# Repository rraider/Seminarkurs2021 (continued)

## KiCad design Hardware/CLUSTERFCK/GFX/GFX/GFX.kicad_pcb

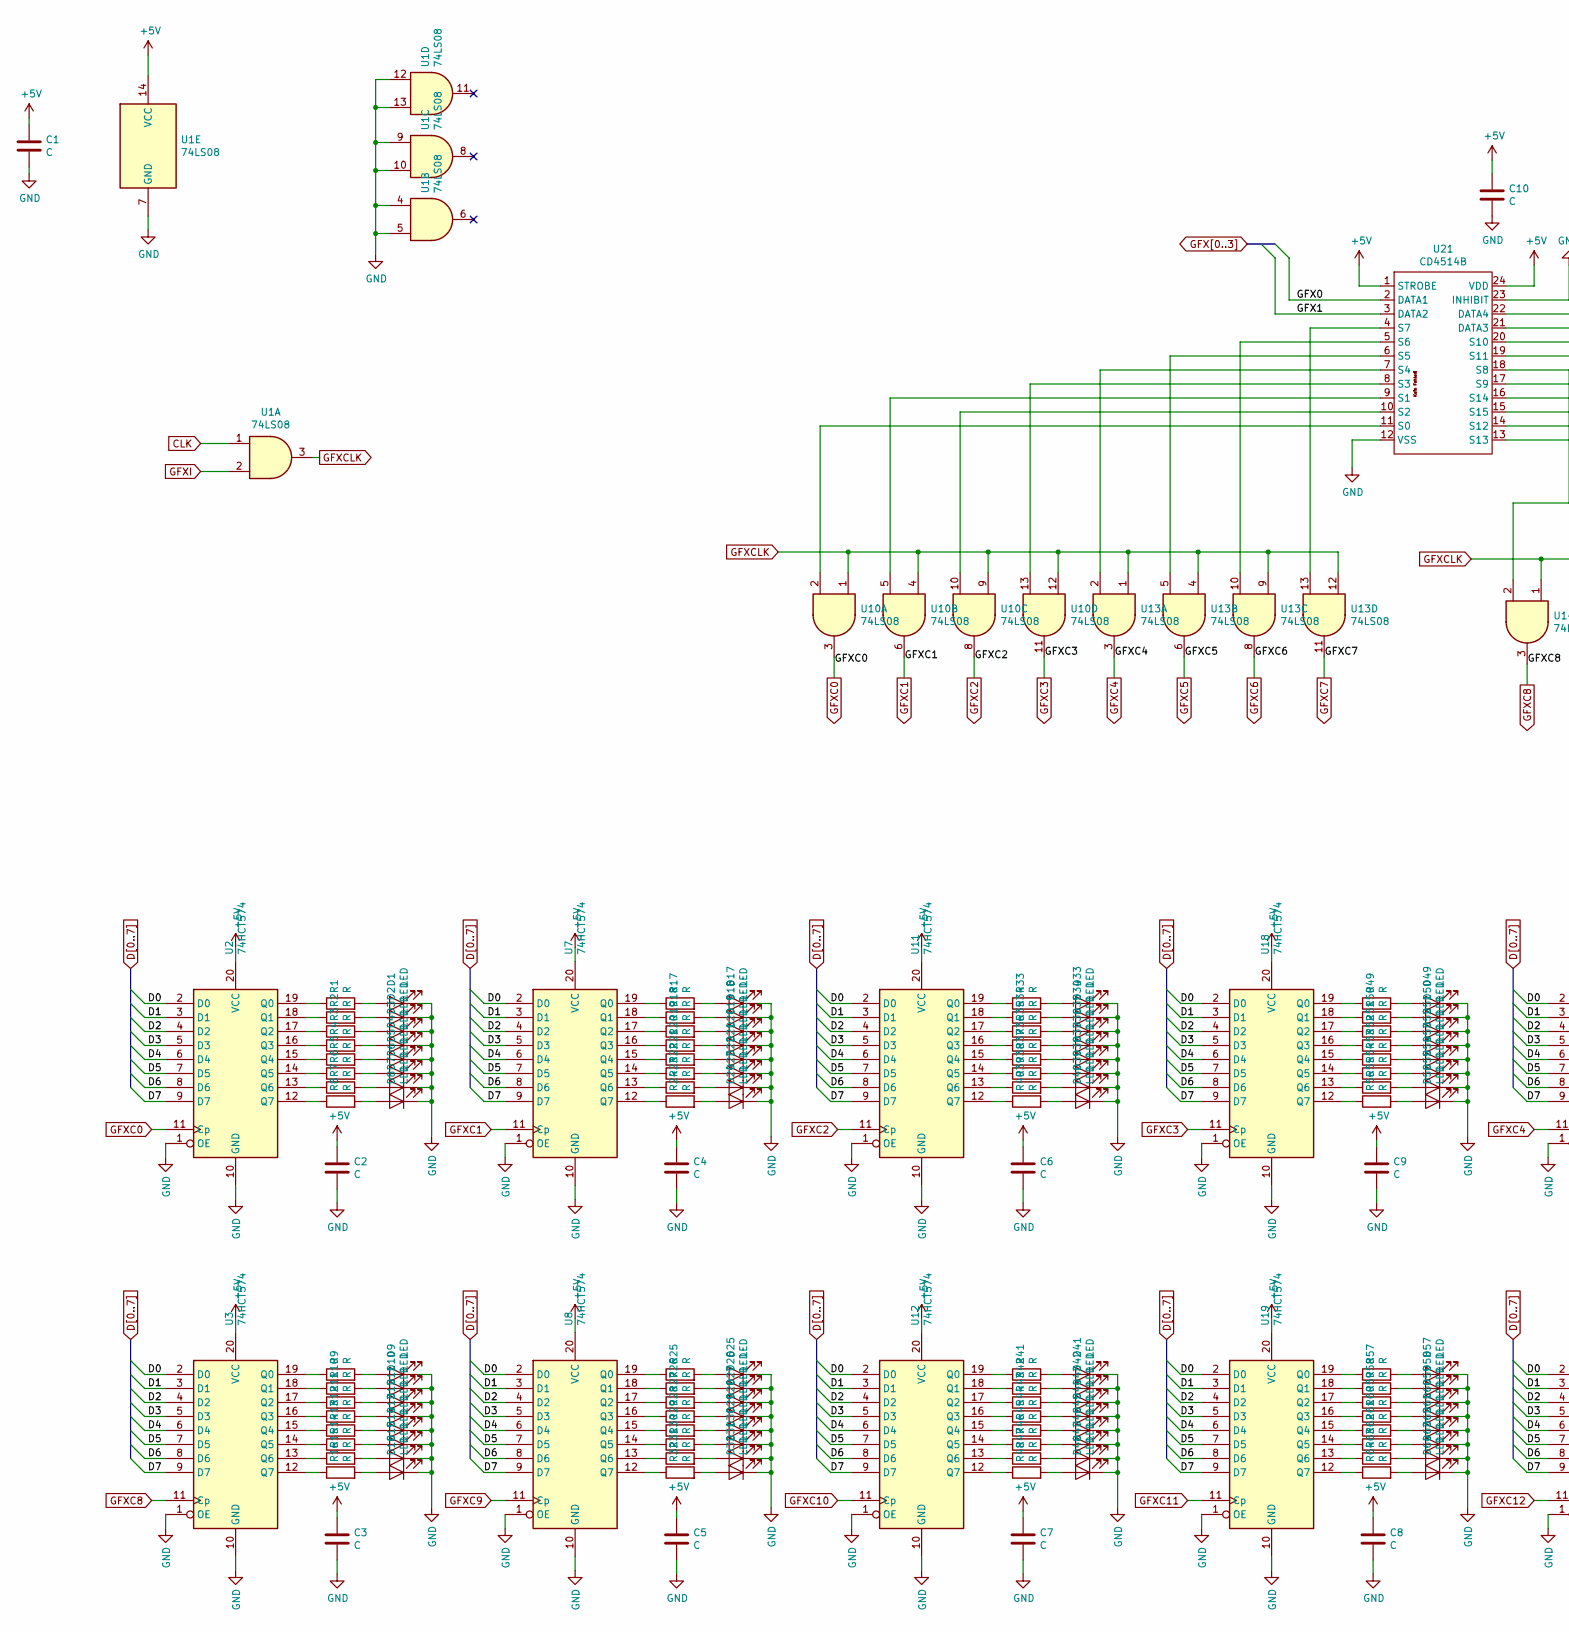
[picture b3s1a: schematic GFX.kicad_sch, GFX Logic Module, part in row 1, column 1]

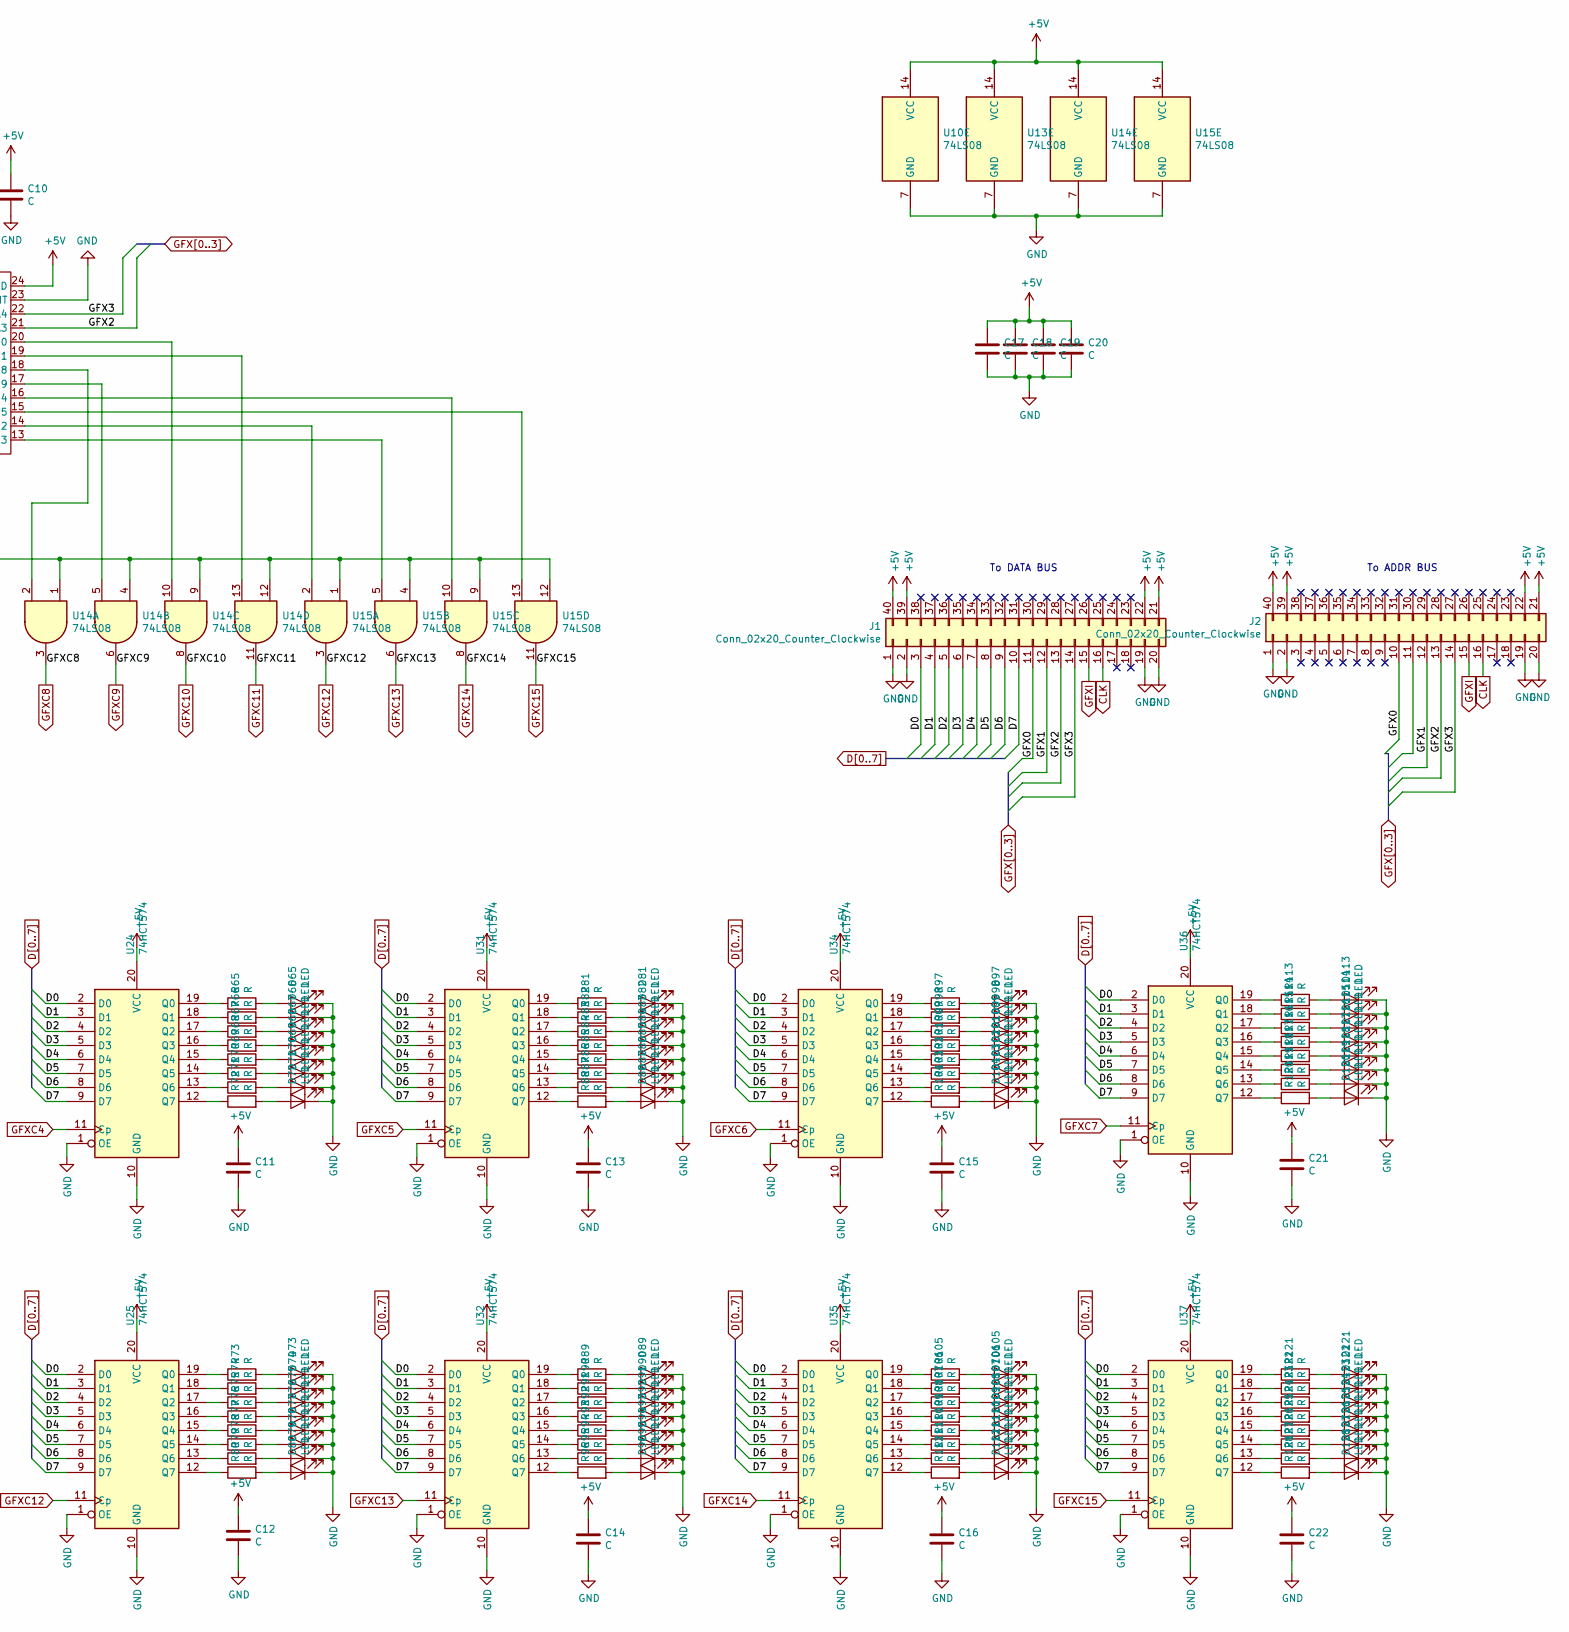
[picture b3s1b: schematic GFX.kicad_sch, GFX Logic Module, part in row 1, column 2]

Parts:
C1, C2, C3, C4, C5, C6, C7, C8, C9, C10, C11, C12, C13, C14, C15, C16, C17, C18, C19, C20, C21, C22: C; C_0805_2012Metric_Pad1.15x1.40mm_HandSolder
D1, D2, D3, D4, D5, D6, D7, D8, D9, D10, D11, D12, D13, D14, D15, D16, D17, D18, D19, D20, D21, D22, D23, D24, D25, D26, D27, D28, D29, D30, D31, D32, D33, D34, D35, D36, D37, D38, D39, D40, D41, D42, D43, D44, D45, D46, D47, D48, D49, D50, D51, D52, D53, D54, D55, D56, D57, D58, D59, D60, D61, D62, D63, D64, D65, D66, D67, D68, D69, D70, D71, D72, D73, D74, D75, D76, D77, D78, D79, D80, D81, D82, D83, D84, D85, D86, D87, D88, D89, D90, D91, D92, D93, D94, D95, D96, D97, D98, D99, D100, D101, D102, D103, D104, D105, D106, D107, D108, D109, D110, D111, D112, D113, D114, D115, D116, D117, D118, D119, D120, D121, D122, D123, D124, D125, D126, D127, D128: LED; LED_D5.0mm
J1, J2: Conn_02x20_Counter_Clockwise; PinSocket_2x20_P2.54mm_Horizontal
R1, R2, R3, R4, R5, R6, R7, R8, R9, R10, R11, R12, R13, R14, R15, R16, R17, R18, R19, R20, R21, R22, R23, R24, R25, R26, R27, R28, R29, R30, R31, R32, R33, R34, R35, R36, R37, R38, R39, R40, R41, R42, R43, R44, R45, R46, R47, R48, R49, R50, R51, R52, R53, R54, R55, R56, R57, R58, R59, R60, R61, R62, R63, R64, R65, R66, R67, R68, R69, R70, R71, R72, R73, R74, R75, R76, R77, R78, R79, R80, R81, R82, R83, R84, R85, R86, R87, R88, R89, R90, R91, R92, R93, R94, R95, R96, R97, R98, R99, R100, R101, R102, R103, R104, R105, R106, R107, R108, R109, R110, R111, R112, R113, R114, R115, R116, R117, R118, R119, R120, R121, R122, R123, R124, R125, R126, R127, R128: R; R_0805_2012Metric_Pad1.15x1.40mm_HandSolder
U1: 74LS08; SOIC-14_3.9x8.7mm_P1.27mm
U2, U3, U7, U8, U11, U12, U18, U19, U24, U25, U31, U32, U34, U35, U36, U37: 74HCT574; SOIC-20W_7.5x12.8mm_P1.27mm
U10, U13, U14, U15: 74LS08
U21: CD4514B; SOIC-24W_7.5x15.4mm_P1.27mm

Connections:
+5V: C1.1, C2.1, C3.1, C4.1, C5.1, C6.1, C7.1, C8.1, C9.1, C10.1, C11.1, C12.1, C13.1, C14.1, C15.1, C16.1, C17.1, C18.1, C19.1, C20.1, C21.1, C22.1, J1.21, J1.22, J1.39, J1.40, J2.21, J2.22, J2.39, J2.40, U1.14 (VCC), U2.20 (VCC), U3.20 (VCC), U7.20 (VCC), U8.20 (VCC), U10.14 (VCC), U11.20 (VCC), U12.20 (VCC), U13.14 (VCC), U14.14 (VCC), U15.14 (VCC), U18.20 (VCC), U19.20 (VCC), U21.1 (STROBE), U21.24 (VDD), U24.20 (VCC), U25.20 (VCC), U31.20 (VCC), U32.20 (VCC), U34.20 (VCC), U35.20 (VCC), U36.20 (VCC), U37.20 (VCC)
CLK: J1.16, J2.16, U1.1
D0: J1.3, U2.2 (D0), U3.2 (D0), U7.2 (D0), U8.2 (D0), U11.2 (D0), U12.2 (D0), U18.2 (D0), U19.2 (D0), U24.2 (D0), U25.2 (D0), U31.2 (D0), U32.2 (D0), U34.2 (D0), U35.2 (D0), U36.2 (D0), U37.2 (D0)
D1: J1.4, U2.3 (D1), U3.3 (D1), U7.3 (D1), U8.3 (D1), U11.3 (D1), U12.3 (D1), U18.3 (D1), U19.3 (D1), U24.3 (D1), U25.3 (D1), U31.3 (D1), U32.3 (D1), U34.3 (D1), U35.3 (D1), U36.3 (D1), U37.3 (D1)
D2: J1.5, U2.4 (D2), U3.4 (D2), U7.4 (D2), U8.4 (D2), U11.4 (D2), U12.4 (D2), U18.4 (D2), U19.4 (D2), U24.4 (D2), U25.4 (D2), U31.4 (D2), U32.4 (D2), U34.4 (D2), U35.4 (D2), U36.4 (D2), U37.4 (D2)
D3: J1.6, U2.5 (D3), U3.5 (D3), U7.5 (D3), U8.5 (D3), U11.5 (D3), U12.5 (D3), U18.5 (D3), U19.5 (D3), U24.5 (D3), U25.5 (D3), U31.5 (D3), U32.5 (D3), U34.5 (D3), U35.5 (D3), U36.5 (D3), U37.5 (D3)
D4: J1.7, U2.6 (D4), U3.6 (D4), U7.6 (D4), U8.6 (D4), U11.6 (D4), U12.6 (D4), U18.6 (D4), U19.6 (D4), U24.6 (D4), U25.6 (D4), U31.6 (D4), U32.6 (D4), U34.6 (D4), U35.6 (D4), U36.6 (D4), U37.6 (D4)
D5: J1.8, U2.7 (D5), U3.7 (D5), U7.7 (D5), U8.7 (D5), U11.7 (D5), U12.7 (D5), U18.7 (D5), U19.7 (D5), U24.7 (D5), U25.7 (D5), U31.7 (D5), U32.7 (D5), U34.7 (D5), U35.7 (D5), U36.7 (D5), U37.7 (D5)
D6: J1.9, U2.8 (D6), U3.8 (D6), U7.8 (D6), U8.8 (D6), U11.8 (D6), U12.8 (D6), U18.8 (D6), U19.8 (D6), U24.8 (D6), U25.8 (D6), U31.8 (D6), U32.8 (D6), U34.8 (D6), U35.8 (D6), U36.8 (D6), U37.8 (D6)
D7: J1.10, U2.9 (D7), U3.9 (D7), U7.9 (D7), U8.9 (D7), U11.9 (D7), U12.9 (D7), U18.9 (D7), U19.9 (D7), U24.9 (D7), U25.9 (D7), U31.9 (D7), U32.9 (D7), U34.9 (D7), U35.9 (D7), U36.9 (D7), U37.9 (D7)
GFX0: J1.11, J2.10, U21.2 (DATA1)
GFX1: J1.12, J2.12, U21.3 (DATA2)
GFX2: J1.13, J2.13, U21.21 (DATA3)
GFX3: J1.14, J2.14, U21.22 (DATA4)
GFXC0: U2.11 (Cp), U10.3
GFXC1: U7.11 (Cp), U10.6
GFXC2: U10.8, U11.11 (Cp)
GFXC3: U10.11, U18.11 (Cp)
GFXC4: U13.3, U24.11 (Cp)
GFXC5: U13.6, U31.11 (Cp)
GFXC6: U13.8, U34.11 (Cp)
GFXC7: U13.11, U36.11 (Cp)
GFXC8: U3.11 (Cp), U14.3
GFXC9: U8.11 (Cp), U14.6
GFXC10: U12.11 (Cp), U14.8
GFXC11: U14.11, U19.11 (Cp)
GFXC12: U15.3, U25.11 (Cp)
GFXC13: U15.6, U32.11 (Cp)
GFXC14: U15.8, U35.11 (Cp)
GFXC15: U15.11, U37.11 (Cp)
GFXCLK: U1.3, U10.1, U10.4, U10.9, U10.12, U13.1, U13.4, U13.9, U13.12, U14.1, U14.4, U14.9, U14.12, U15.1, U15.4, U15.9, U15.12
GFXI: J1.15, J2.15, U1.2
GND: C1.2, C2.2, C3.2, C4.2, C5.2, C6.2, C7.2, C8.2, C9.2, C10.2, C11.2, C12.2, C13.2, C14.2, C15.2, C16.2, C17.2, C18.2, C19.2, C20.2, C21.2, C22.2, D1.1 (K), D2.1 (K), D3.1 (K), D4.1 (K), D5.1 (K), D6.1 (K), D7.1 (K), D8.1 (K), D9.1 (K), D10.1 (K), D11.1 (K), D12.1 (K), D13.1 (K), D14.1 (K), D15.1 (K), D16.1 (K), D17.1 (K), D18.1 (K), D19.1 (K), D20.1 (K), D21.1 (K), D22.1 (K), D23.1 (K), D24.1 (K), D25.1 (K), D26.1 (K), D27.1 (K), D28.1 (K), D29.1 (K), D30.1 (K), D31.1 (K), D32.1 (K), D33.1 (K), D34.1 (K), D35.1 (K), D36.1 (K), D37.1 (K), D38.1 (K), D39.1 (K), D40.1 (K), D41.1 (K), D42.1 (K), D43.1 (K), D44.1 (K), D45.1 (K), D46.1 (K), D47.1 (K), D48.1 (K), D49.1 (K), D50.1 (K), D51.1 (K), D52.1 (K), D53.1 (K), D54.1 (K), D55.1 (K), D56.1 (K), D57.1 (K), D58.1 (K), D59.1 (K), D60.1 (K), D61.1 (K), D62.1 (K), D63.1 (K), D64.1 (K), D65.1 (K), D66.1 (K), D67.1 (K), D68.1 (K), D69.1 (K), D70.1 (K), D71.1 (K), D72.1 (K), D73.1 (K), D74.1 (K), D75.1 (K), D76.1 (K), D77.1 (K), D78.1 (K), D79.1 (K), D80.1 (K), D81.1 (K), D82.1 (K), D83.1 (K), D84.1 (K), D85.1 (K), D86.1 (K), D87.1 (K), D88.1 (K), D89.1 (K), D90.1 (K), D91.1 (K), D92.1 (K), D93.1 (K), D94.1 (K), D95.1 (K), D96.1 (K), D97.1 (K), D98.1 (K), D99.1 (K), D100.1 (K), D101.1 (K), D102.1 (K), D103.1 (K), D104.1 (K), D105.1 (K), D106.1 (K), D107.1 (K), D108.1 (K), D109.1 (K), D110.1 (K), D111.1 (K), D112.1 (K), D113.1 (K), D114.1 (K), D115.1 (K), D116.1 (K), D117.1 (K), D118.1 (K), D119.1 (K), D120.1 (K), D121.1 (K), D122.1 (K), D123.1 (K), D124.1 (K), D125.1 (K), D126.1 (K), D127.1 (K), D128.1 (K), J1.1, J1.2, J1.19, J1.20, J2.1, J2.2, J2.19, J2.20, U1.4, U1.5, U1.7 (GND), U1.9, U1.10, U1.12, U1.13, U2.1 (OE), U2.10 (GND), U3.1 (OE), U3.10 (GND), U7.1 (OE), U7.10 (GND), U8.1 (OE), U8.10 (GND), U10.7 (GND), U11.1 (OE), U11.10 (GND), U12.1 (OE), U12.10 (GND), U13.7 (GND), U14.7 (GND), U15.7 (GND), U18.1 (OE), U18.10 (GND), U19.1 (OE), U19.10 (GND), U21.12 (VSS), U21.23 (INHIBIT), U24.1 (OE), U24.10 (GND), U25.1 (OE), U25.10 (GND), U31.1 (OE), U31.10 (GND), U32.1 (OE), U32.10 (GND), U34.1 (OE), U34.10 (GND), U35.1 (OE), U35.10 (GND), U36.1 (OE), U36.10 (GND), U37.1 (OE), U37.10 (GND)
unnamed: D1.2 (A), R1.2
unnamed: D2.2 (A), R2.2
unnamed: D3.2 (A), R3.2
unnamed: D4.2 (A), R4.2
unnamed: D5.2 (A), R5.2
unnamed: D6.2 (A), R6.2
unnamed: D7.2 (A), R7.2
unnamed: D8.2 (A), R8.2
unnamed: D9.2 (A), R9.2
unnamed: D10.2 (A), R10.2
unnamed: D11.2 (A), R11.2
unnamed: D12.2 (A), R12.2
unnamed: D13.2 (A), R13.2
unnamed: D14.2 (A), R14.2
unnamed: D15.2 (A), R15.2
unnamed: D16.2 (A), R16.2
unnamed: D17.2 (A), R17.2
unnamed: D18.2 (A), R18.2
unnamed: D19.2 (A), R19.2
unnamed: D20.2 (A), R20.2
unnamed: D21.2 (A), R21.2
unnamed: D22.2 (A), R22.2
unnamed: D23.2 (A), R23.2
unnamed: D24.2 (A), R24.2
unnamed: D25.2 (A), R25.2
unnamed: D26.2 (A), R26.2
unnamed: D27.2 (A), R27.2
unnamed: D28.2 (A), R28.2
unnamed: D29.2 (A), R29.2
unnamed: D30.2 (A), R30.2
unnamed: D31.2 (A), R31.2
unnamed: D32.2 (A), R32.2
unnamed: D33.2 (A), R33.2
unnamed: D34.2 (A), R34.2
unnamed: D35.2 (A), R35.2
unnamed: D36.2 (A), R36.2
unnamed: D37.2 (A), R37.2
unnamed: D38.2 (A), R38.2
unnamed: D39.2 (A), R39.2
unnamed: D40.2 (A), R40.2
unnamed: D41.2 (A), R41.2
unnamed: D42.2 (A), R42.2
unnamed: D43.2 (A), R43.2
unnamed: D44.2 (A), R44.2
unnamed: D45.2 (A), R45.2
unnamed: D46.2 (A), R46.2
unnamed: D47.2 (A), R47.2
unnamed: D48.2 (A), R48.2
unnamed: D49.2 (A), R49.2
unnamed: D50.2 (A), R50.2
unnamed: D51.2 (A), R51.2
unnamed: D52.2 (A), R52.2
unnamed: D53.2 (A), R53.2
unnamed: D54.2 (A), R54.2
unnamed: D55.2 (A), R55.2
unnamed: D56.2 (A), R56.2
unnamed: D57.2 (A), R57.2
unnamed: D58.2 (A), R58.2
unnamed: D59.2 (A), R59.2
unnamed: D60.2 (A), R60.2
unnamed: D61.2 (A), R61.2
unnamed: D62.2 (A), R62.2
unnamed: D63.2 (A), R63.2
unnamed: D64.2 (A), R64.2
unnamed: D65.2 (A), R65.2
unnamed: D66.2 (A), R66.2
unnamed: D67.2 (A), R67.2
unnamed: D68.2 (A), R68.2
unnamed: D69.2 (A), R69.2
unnamed: D70.2 (A), R70.2
unnamed: D71.2 (A), R71.2
unnamed: D72.2 (A), R72.2
unnamed: D73.2 (A), R73.2
unnamed: D74.2 (A), R74.2
unnamed: D75.2 (A), R75.2
unnamed: D76.2 (A), R76.2
unnamed: D77.2 (A), R77.2
unnamed: D78.2 (A), R78.2
unnamed: D79.2 (A), R79.2
unnamed: D80.2 (A), R80.2
unnamed: D81.2 (A), R81.2
unnamed: D82.2 (A), R82.2
unnamed: D83.2 (A), R83.2
unnamed: D84.2 (A), R84.2
unnamed: D85.2 (A), R85.2
unnamed: D86.2 (A), R86.2
unnamed: D87.2 (A), R87.2
unnamed: D88.2 (A), R88.2
unnamed: D89.2 (A), R89.2
unnamed: D90.2 (A), R90.2
unnamed: D91.2 (A), R91.2
unnamed: D92.2 (A), R92.2
unnamed: D93.2 (A), R93.2
unnamed: D94.2 (A), R94.2
unnamed: D95.2 (A), R95.2
unnamed: D96.2 (A), R96.2
unnamed: D97.2 (A), R97.2
unnamed: D98.2 (A), R98.2
unnamed: D99.2 (A), R99.2
unnamed: D100.2 (A), R100.2
unnamed: D101.2 (A), R101.2
unnamed: D102.2 (A), R102.2
unnamed: D103.2 (A), R103.2
unnamed: D104.2 (A), R104.2
unnamed: D105.2 (A), R105.2
unnamed: D106.2 (A), R106.2
unnamed: D107.2 (A), R107.2
unnamed: D108.2 (A), R108.2
unnamed: D109.2 (A), R109.2
unnamed: D110.2 (A), R110.2
unnamed: D111.2 (A), R111.2
unnamed: D112.2 (A), R112.2
unnamed: D113.2 (A), R113.2
unnamed: D114.2 (A), R114.2
unnamed: D115.2 (A), R115.2
unnamed: D116.2 (A), R116.2
unnamed: D117.2 (A), R117.2
unnamed: D118.2 (A), R118.2
unnamed: D119.2 (A), R119.2
unnamed: D120.2 (A), R120.2
unnamed: D121.2 (A), R121.2
unnamed: D122.2 (A), R122.2
unnamed: D123.2 (A), R123.2
unnamed: D124.2 (A), R124.2
unnamed: D125.2 (A), R125.2
unnamed: D126.2 (A), R126.2
unnamed: D127.2 (A), R127.2
unnamed: D128.2 (A), R128.2
unnamed: R1.1, U2.19 (Q0)
unnamed: R2.1, U2.18 (Q1)
unnamed: R3.1, U2.17 (Q2)
unnamed: R4.1, U2.16 (Q3)
unnamed: R5.1, U2.15 (Q4)
unnamed: R6.1, U2.14 (Q5)
unnamed: R7.1, U2.13 (Q6)
unnamed: R8.1, U2.12 (Q7)
unnamed: R9.1, U3.19 (Q0)
unnamed: R10.1, U3.18 (Q1)
unnamed: R11.1, U3.17 (Q2)
unnamed: R12.1, U3.16 (Q3)
unnamed: R13.1, U3.15 (Q4)
unnamed: R14.1, U3.14 (Q5)
unnamed: R15.1, U3.13 (Q6)
unnamed: R16.1, U3.12 (Q7)
unnamed: R17.1, U7.19 (Q0)
unnamed: R18.1, U7.18 (Q1)
unnamed: R19.1, U7.17 (Q2)
unnamed: R20.1, U7.16 (Q3)
unnamed: R21.1, U7.15 (Q4)
unnamed: R22.1, U7.14 (Q5)
unnamed: R23.1, U7.13 (Q6)
unnamed: R24.1, U7.12 (Q7)
unnamed: R25.1, U8.19 (Q0)
unnamed: R26.1, U8.18 (Q1)
unnamed: R27.1, U8.17 (Q2)
unnamed: R28.1, U8.16 (Q3)
unnamed: R29.1, U8.15 (Q4)
unnamed: R30.1, U8.14 (Q5)
unnamed: R31.1, U8.13 (Q6)
unnamed: R32.1, U8.12 (Q7)
unnamed: R33.1, U11.19 (Q0)
unnamed: R34.1, U11.18 (Q1)
unnamed: R35.1, U11.17 (Q2)
unnamed: R36.1, U11.16 (Q3)
unnamed: R37.1, U11.15 (Q4)
unnamed: R38.1, U11.14 (Q5)
unnamed: R39.1, U11.13 (Q6)
unnamed: R40.1, U11.12 (Q7)
unnamed: R41.1, U12.19 (Q0)
unnamed: R42.1, U12.18 (Q1)
unnamed: R43.1, U12.17 (Q2)
unnamed: R44.1, U12.16 (Q3)
unnamed: R45.1, U12.15 (Q4)
unnamed: R46.1, U12.14 (Q5)
unnamed: R47.1, U12.13 (Q6)
unnamed: R48.1, U12.12 (Q7)
unnamed: R49.1, U18.19 (Q0)
unnamed: R50.1, U18.18 (Q1)
unnamed: R51.1, U18.17 (Q2)
unnamed: R52.1, U18.16 (Q3)
unnamed: R53.1, U18.15 (Q4)
unnamed: R54.1, U18.14 (Q5)
unnamed: R55.1, U18.13 (Q6)
unnamed: R56.1, U18.12 (Q7)
unnamed: R57.1, U19.19 (Q0)
unnamed: R58.1, U19.18 (Q1)
unnamed: R59.1, U19.17 (Q2)
unnamed: R60.1, U19.16 (Q3)
unnamed: R61.1, U19.15 (Q4)
unnamed: R62.1, U19.14 (Q5)
unnamed: R63.1, U19.13 (Q6)
unnamed: R64.1, U19.12 (Q7)
unnamed: R65.1, U24.19 (Q0)
unnamed: R66.1, U24.18 (Q1)
unnamed: R67.1, U24.17 (Q2)
unnamed: R68.1, U24.16 (Q3)
unnamed: R69.1, U24.15 (Q4)
unnamed: R70.1, U24.14 (Q5)
unnamed: R71.1, U24.13 (Q6)
unnamed: R72.1, U24.12 (Q7)
unnamed: R73.1, U25.19 (Q0)
unnamed: R74.1, U25.18 (Q1)
unnamed: R75.1, U25.17 (Q2)
unnamed: R76.1, U25.16 (Q3)
unnamed: R77.1, U25.15 (Q4)
unnamed: R78.1, U25.14 (Q5)
unnamed: R79.1, U25.13 (Q6)
unnamed: R80.1, U25.12 (Q7)
unnamed: R81.1, U31.19 (Q0)
unnamed: R82.1, U31.18 (Q1)
unnamed: R83.1, U31.17 (Q2)
unnamed: R84.1, U31.16 (Q3)
unnamed: R85.1, U31.15 (Q4)
unnamed: R86.1, U31.14 (Q5)
unnamed: R87.1, U31.13 (Q6)
unnamed: R88.1, U31.12 (Q7)
unnamed: R89.1, U32.19 (Q0)
unnamed: R90.1, U32.18 (Q1)
unnamed: R91.1, U32.17 (Q2)
unnamed: R92.1, U32.16 (Q3)
unnamed: R93.1, U32.15 (Q4)
unnamed: R94.1, U32.14 (Q5)
unnamed: R95.1, U32.13 (Q6)
unnamed: R96.1, U32.12 (Q7)
unnamed: R97.1, U34.19 (Q0)
unnamed: R98.1, U34.18 (Q1)
unnamed: R99.1, U34.17 (Q2)
unnamed: R100.1, U34.16 (Q3)
unnamed: R101.1, U34.15 (Q4)
unnamed: R102.1, U34.14 (Q5)
unnamed: R103.1, U34.13 (Q6)
unnamed: R104.1, U34.12 (Q7)
unnamed: R105.1, U35.19 (Q0)
unnamed: R106.1, U35.18 (Q1)
unnamed: R107.1, U35.17 (Q2)
unnamed: R108.1, U35.16 (Q3)
unnamed: R109.1, U35.15 (Q4)
unnamed: R110.1, U35.14 (Q5)
unnamed: R111.1, U35.13 (Q6)
unnamed: R112.1, U35.12 (Q7)
unnamed: R113.1, U36.19 (Q0)
unnamed: R114.1, U36.18 (Q1)
unnamed: R115.1, U36.17 (Q2)
unnamed: R116.1, U36.16 (Q3)
unnamed: R117.1, U36.15 (Q4)
unnamed: R118.1, U36.14 (Q5)
unnamed: R119.1, U36.13 (Q6)
unnamed: R120.1, U36.12 (Q7)
unnamed: R121.1, U37.19 (Q0)
unnamed: R122.1, U37.18 (Q1)
unnamed: R123.1, U37.17 (Q2)
unnamed: R124.1, U37.16 (Q3)
unnamed: R125.1, U37.15 (Q4)
unnamed: R126.1, U37.14 (Q5)
unnamed: R127.1, U37.13 (Q6)
unnamed: R128.1, U37.12 (Q7)
unnamed: U10.2, U21.11 (S0)
unnamed: U10.5, U21.9 (S1)
unnamed: U10.10, U21.10 (S2)
unnamed: U10.13, U21.8 (S3)
unnamed: U13.2, U21.7 (S4)
unnamed: U13.5, U21.6 (S5)
unnamed: U13.10, U21.5 (S6)
unnamed: U13.13, U21.4 (S7)
unnamed: U14.2, U21.18 (S8)
unnamed: U14.5, U21.17 (S9)
unnamed: U14.10, U21.20 (S10)
unnamed: U14.13, U21.19 (S11)
unnamed: U15.2, U21.14 (S12)
unnamed: U15.5, U21.13 (S13)
unnamed: U15.10, U21.16 (S14)
unnamed: U15.13, U21.15 (S15)

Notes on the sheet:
To DATA BUS
To ADDR BUS

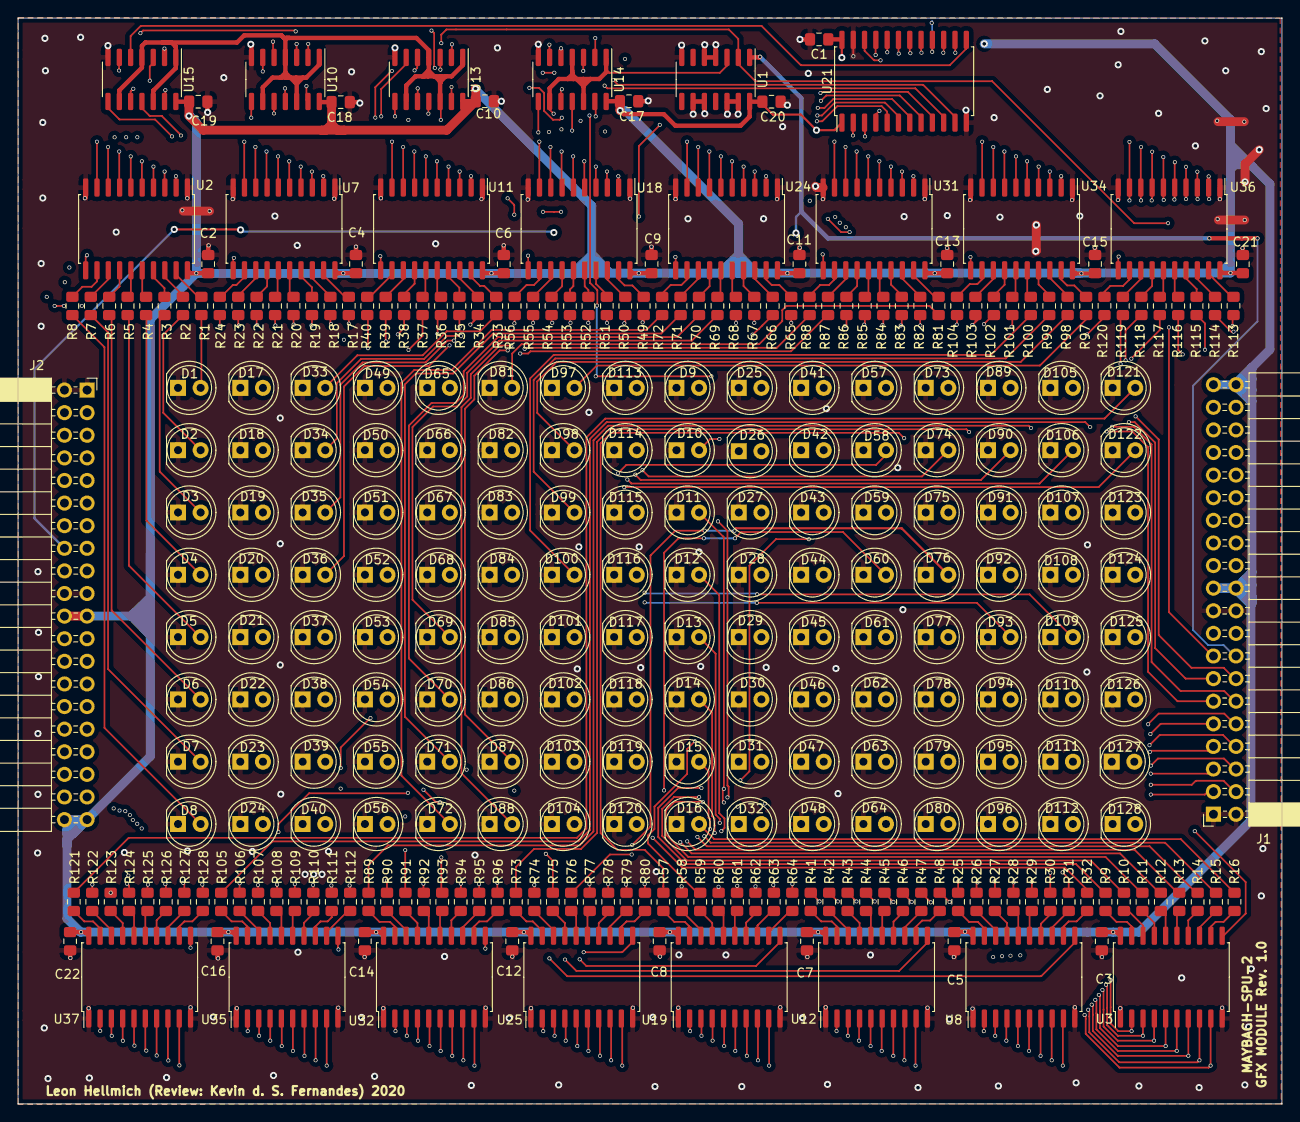
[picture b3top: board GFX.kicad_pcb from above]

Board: 4 copper layers, 142.0 x 122.0 mm, 302 parts (0 on the bottom side), 305 nets.

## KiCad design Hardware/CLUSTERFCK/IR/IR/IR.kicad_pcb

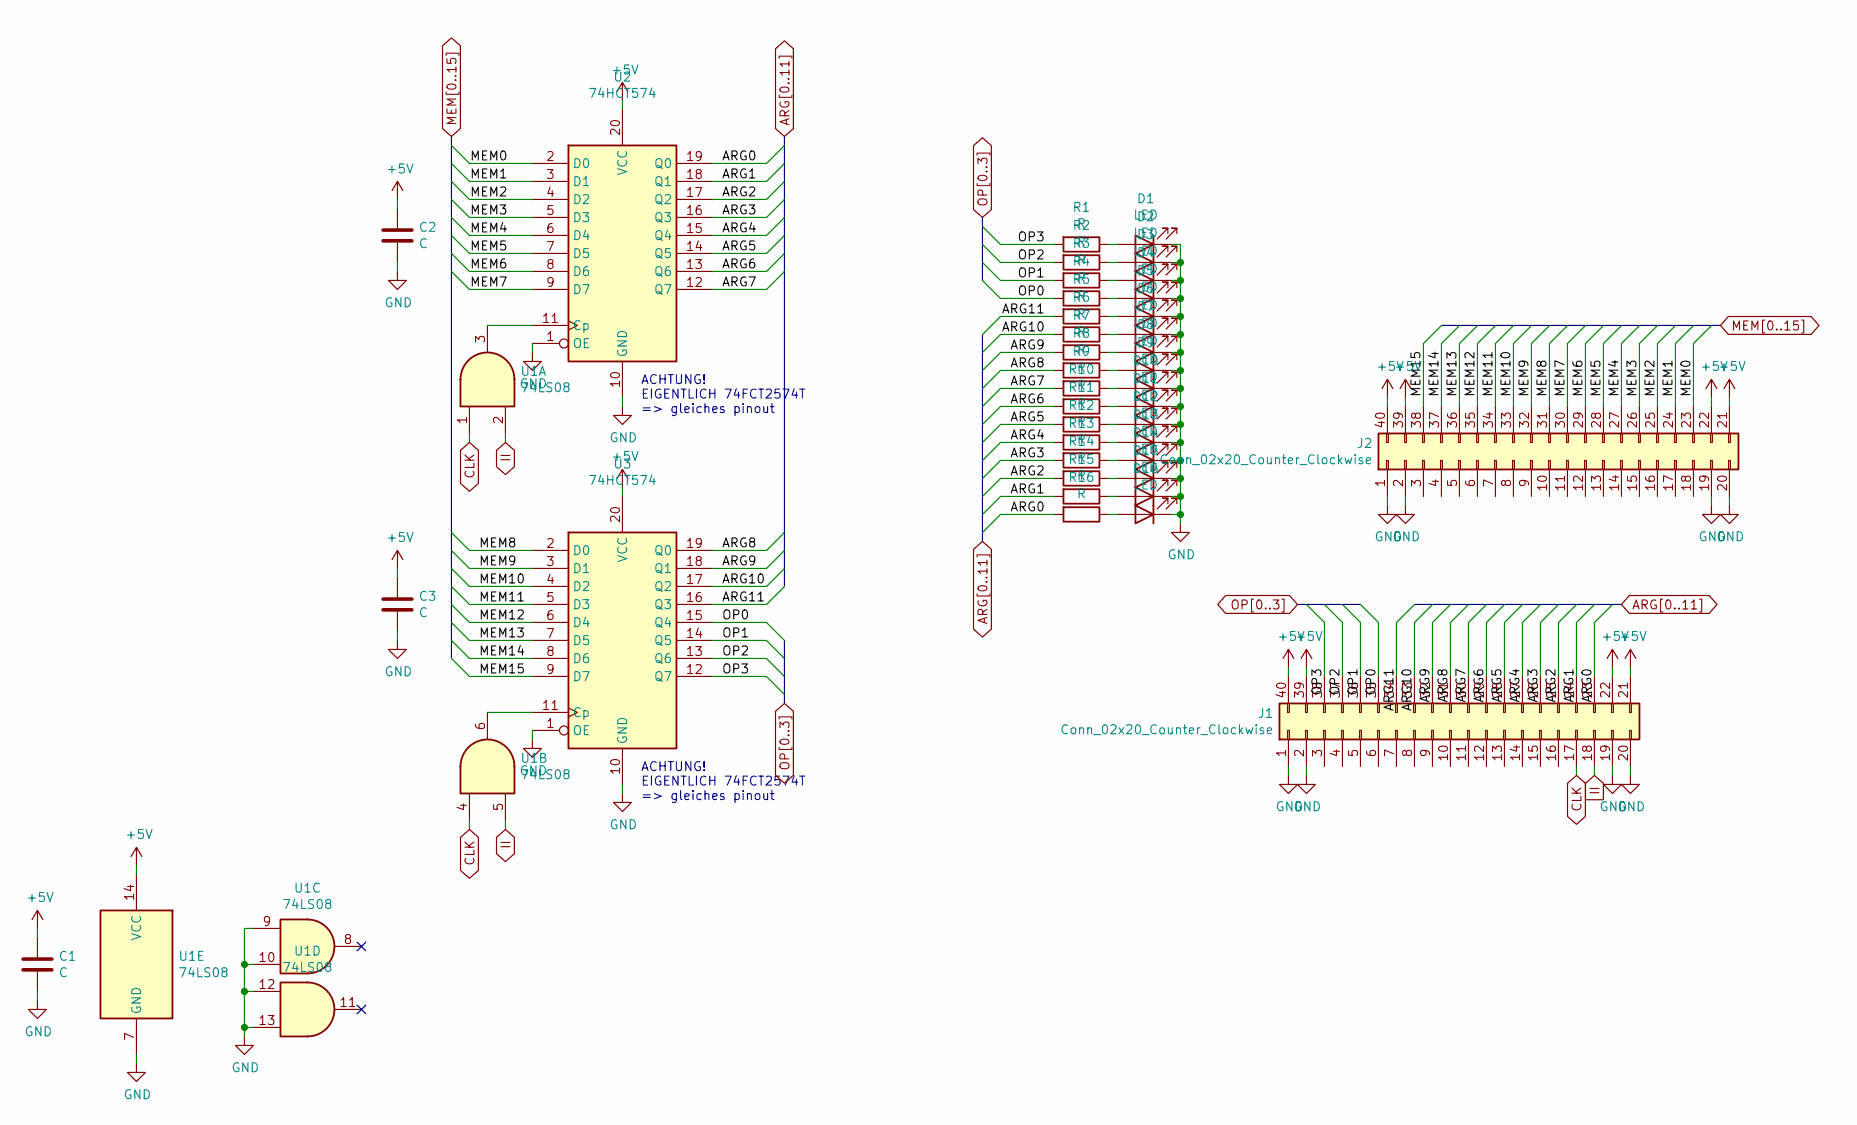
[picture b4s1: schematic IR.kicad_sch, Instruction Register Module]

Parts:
C1, C2, C3: C; C_0805_2012Metric_Pad1.15x1.40mm_HandSolder
D1, D2, D3, D4, D5, D6, D7, D8, D9, D10, D11, D12, D13, D14, D15, D16: LED; LED_D5.0mm
J1, J2: Conn_02x20_Counter_Clockwise; PinSocket_2x20_P2.54mm_Horizontal
R1, R2, R3, R4, R5, R6, R7, R8, R9, R10, R11, R12, R13, R14, R15, R16: R; R_0805_2012Metric_Pad1.15x1.40mm_HandSolder
U1: 74LS08; SOIC-14_3.9x8.7mm_P1.27mm
U2, U3: 74HCT574; SOIC-20W_7.5x12.8mm_P1.27mm

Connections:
+5V: C1.1, C2.1, C3.1, J1.21, J1.22, J1.39, J1.40, J2.21, J2.22, J2.39, J2.40, U1.14 (VCC), U2.20 (VCC), U3.20 (VCC)
ARG0: J1.23, R16.2, U2.19 (Q0)
ARG1: J1.24, R15.2, U2.18 (Q1)
ARG2: J1.25, R14.2, U2.17 (Q2)
ARG3: J1.26, R13.2, U2.16 (Q3)
ARG4: J1.27, R12.2, U2.15 (Q4)
ARG5: J1.28, R11.2, U2.14 (Q5)
ARG6: J1.29, R10.2, U2.13 (Q6)
ARG7: J1.30, R9.2, U2.12 (Q7)
ARG8: J1.31, R8.2, U3.19 (Q0)
ARG9: J1.32, R7.2, U3.18 (Q1)
ARG10: J1.33, R6.2, U3.17 (Q2)
ARG11: J1.34, R5.2, U3.16 (Q3)
CLK: J1.17, U1.1, U1.4
GND: C1.2, C2.2, C3.2, D1.1 (K), D2.1 (K), D3.1 (K), D4.1 (K), D5.1 (K), D6.1 (K), D7.1 (K), D8.1 (K), D9.1 (K), D10.1 (K), D11.1 (K), D12.1 (K), D13.1 (K), D14.1 (K), D15.1 (K), D16.1 (K), J1.1, J1.2, J1.19, J1.20, J2.1, J2.2, J2.19, J2.20, U1.7 (GND), U1.9, U1.10, U1.12, U1.13, U2.1 (OE), U2.10 (GND), U3.1 (OE), U3.10 (GND)
II: J1.18, U1.2, U1.5
MEM0: J2.23, U2.2 (D0)
MEM1: J2.24, U2.3 (D1)
MEM2: J2.25, U2.4 (D2)
MEM3: J2.26, U2.5 (D3)
MEM4: J2.27, U2.6 (D4)
MEM5: J2.28, U2.7 (D5)
MEM6: J2.29, U2.8 (D6)
MEM7: J2.30, U2.9 (D7)
MEM8: J2.31, U3.2 (D0)
MEM9: J2.32, U3.3 (D1)
MEM10: J2.33, U3.4 (D2)
MEM11: J2.34, U3.5 (D3)
MEM12: J2.35, U3.6 (D4)
MEM13: J2.36, U3.7 (D5)
MEM14: J2.37, U3.8 (D6)
MEM15: J2.38, U3.9 (D7)
unnamed: D1.2 (A), R1.1
unnamed: D2.2 (A), R2.1
unnamed: D3.2 (A), R3.1
unnamed: D4.2 (A), R4.1
unnamed: D5.2 (A), R5.1
unnamed: D6.2 (A), R6.1
unnamed: D7.2 (A), R7.1
unnamed: D8.2 (A), R8.1
unnamed: D9.2 (A), R9.1
unnamed: D10.2 (A), R10.1
unnamed: D11.2 (A), R11.1
unnamed: D12.2 (A), R12.1
unnamed: D13.2 (A), R13.1
unnamed: D14.2 (A), R14.1
unnamed: D15.2 (A), R15.1
unnamed: D16.2 (A), R16.1
unnamed: U1.3, U2.11 (Cp)
unnamed: U1.6, U3.11 (Cp)
OP0: J1.35, R4.2, U3.15 (Q4)
OP1: J1.36, R3.2, U3.14 (Q5)
OP2: J1.37, R2.2, U3.13 (Q6)
OP3: J1.38, R1.2, U3.12 (Q7)

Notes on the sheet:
ACHTUNG! EIGENTLICH 74FCT2574T => gleiches pinout

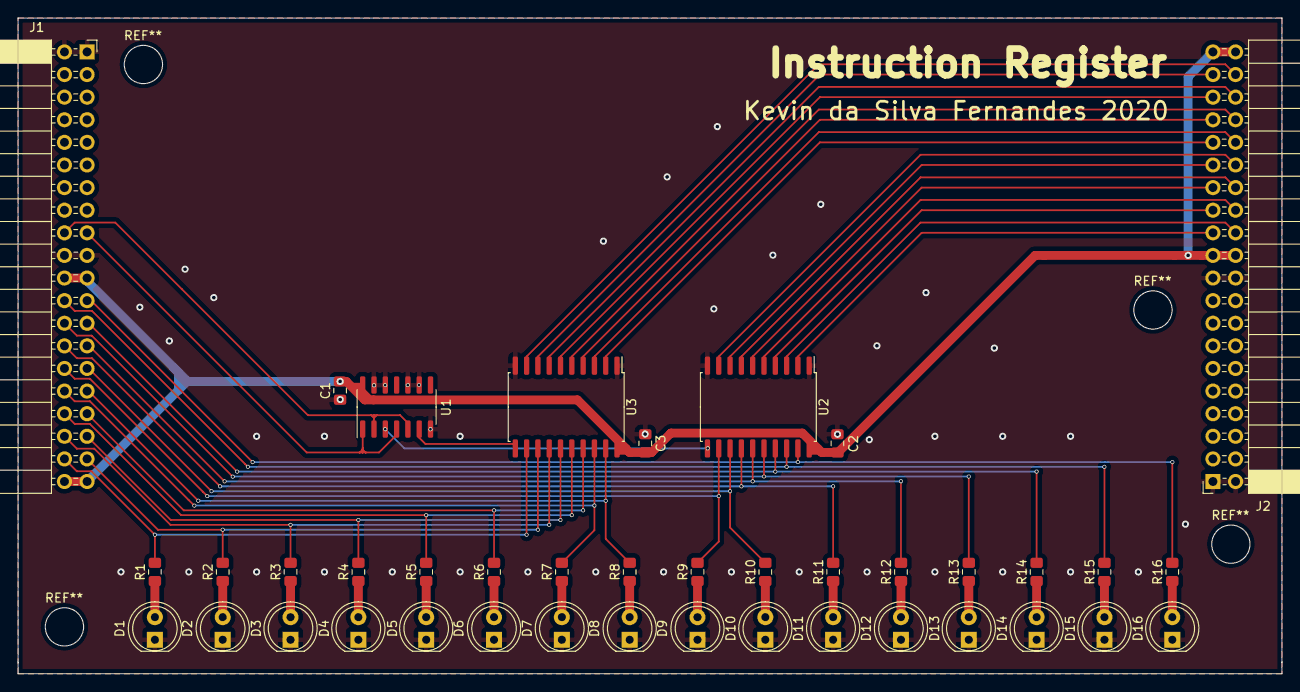
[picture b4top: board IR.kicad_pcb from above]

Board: 2 copper layers, 142.0 x 73.7 mm, 40 parts (0 on the bottom side), 54 nets.

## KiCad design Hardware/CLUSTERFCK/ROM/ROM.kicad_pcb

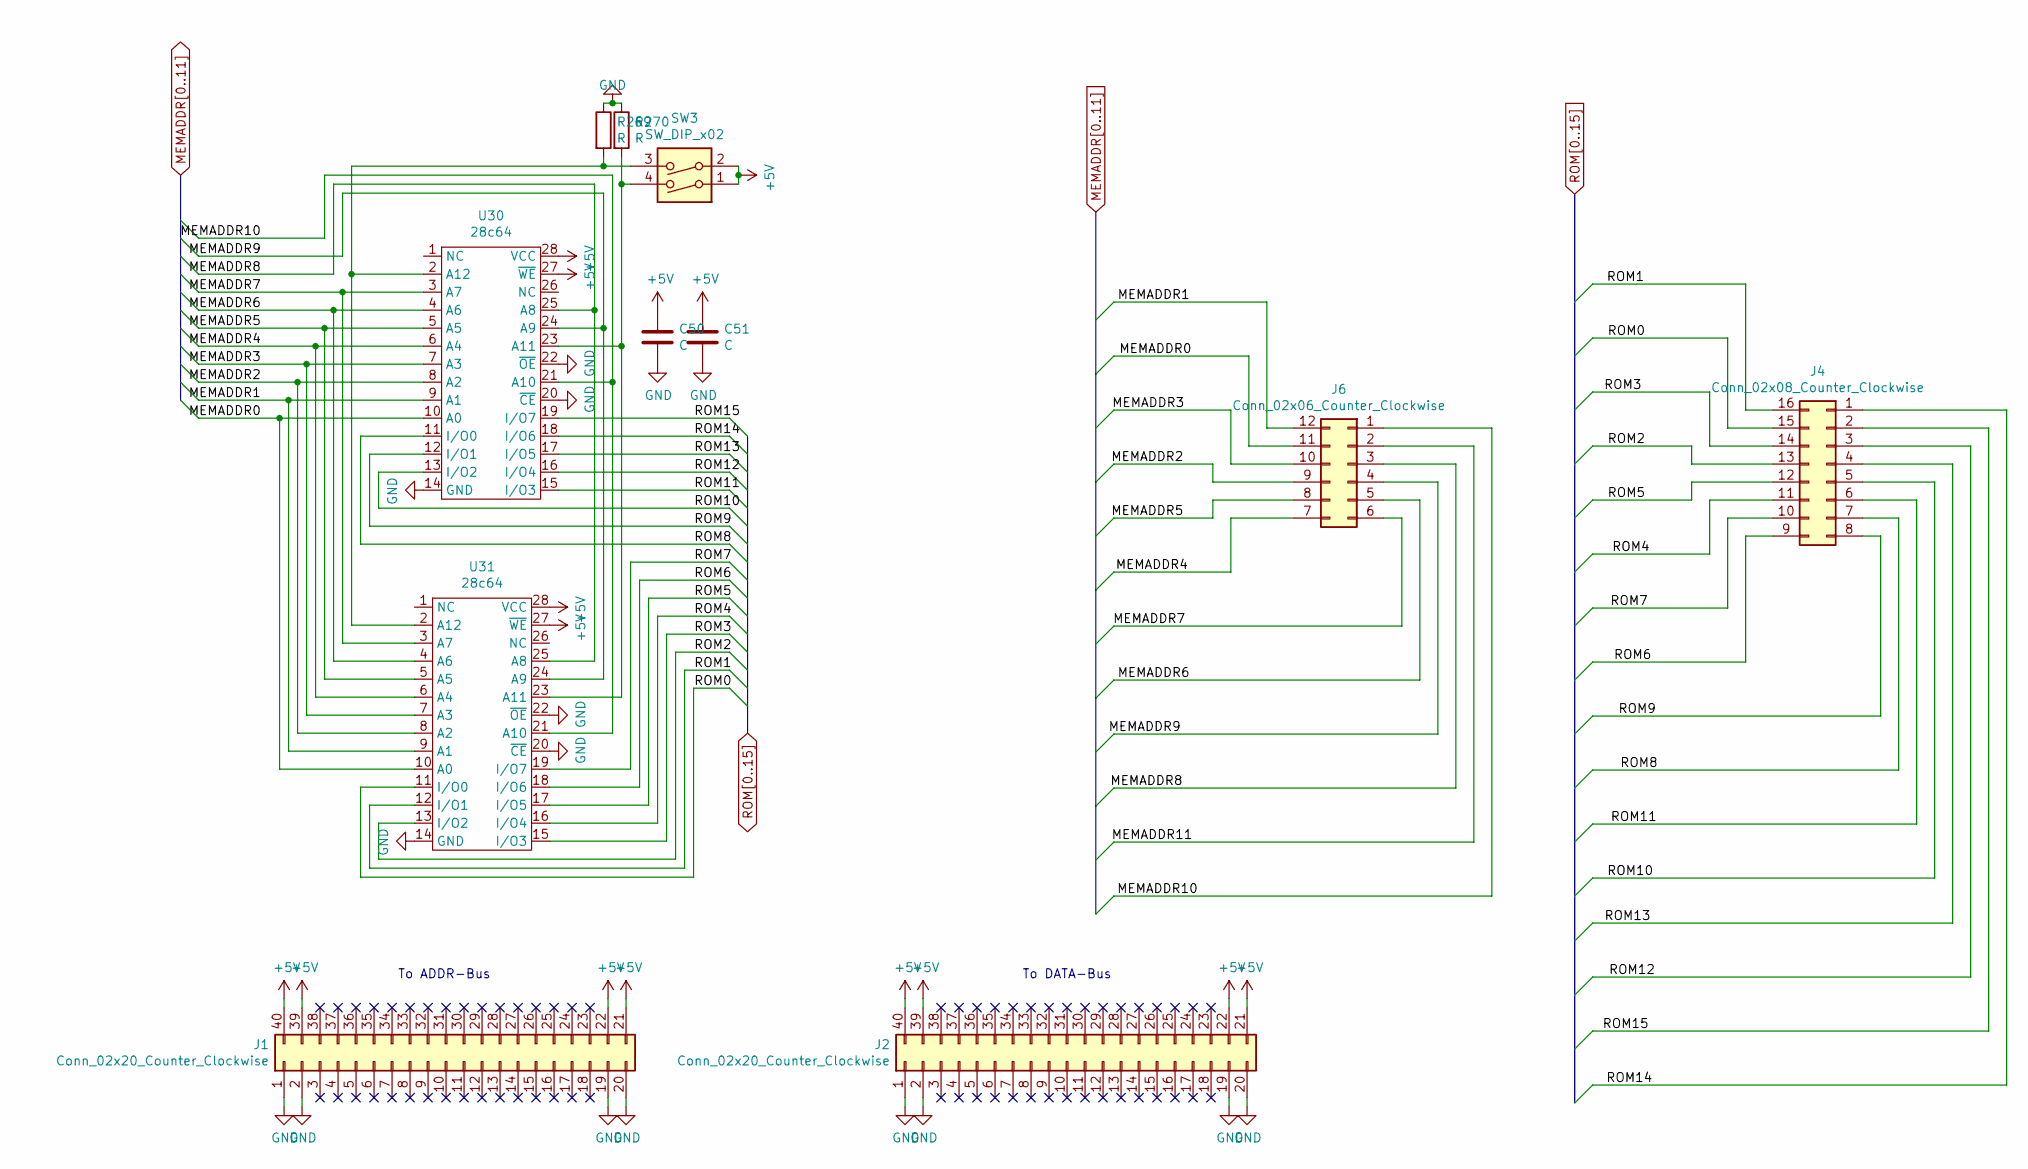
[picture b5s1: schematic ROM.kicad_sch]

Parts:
C50, C51: C; C_0805_2012Metric_Pad1.15x1.40mm_HandSolder
J1, J2: Conn_02x20_Counter_Clockwise; PinSocket_2x20_P2.54mm_Horizontal
J4: Conn_02x08_Counter_Clockwise; PinHeader_2x08_P2.54mm_Horizontal
J6: Conn_02x06_Counter_Clockwise; PinHeader_2x06_P2.54mm_Horizontal
R269, R270: R; R_0805_2012Metric_Pad1.15x1.40mm_HandSolder
SW3: SW_DIP_x02; SW_DIP_SPSTx02_Slide_9.78x7.26mm_W7.62mm_P2.54mm
U30, U31: 28c64; DIP-28_W15.24mm_Socket_LongPads

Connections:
+5V: C50.1, C51.1, J1.21, J1.22, J1.39, J1.40, J2.21, J2.22, J2.39, J2.40, SW3.1, SW3.2, U30.27 (~WE), U30.28 (VCC), U31.27 (~WE), U31.28 (VCC)
GND: C50.2, C51.2, J1.1, J1.2, J1.19, J1.20, J2.1, J2.2, J2.19, J2.20, R269.1, R270.1, U30.14 (GND), U30.20 (~CE), U30.22 (~OE), U31.14 (GND), U31.20 (~CE), U31.22 (~OE)
MEMADDR0: J6.11, U30.10 (A0), U31.10 (A0)
MEMADDR1: J6.12, U30.9 (A1), U31.9 (A1)
MEMADDR2: J6.9, U30.8 (A2), U31.8 (A2)
MEMADDR3: J6.10, U30.7 (A3), U31.7 (A3)
MEMADDR4: J6.7, U30.6 (A4), U31.6 (A4)
MEMADDR5: J6.8, U30.5 (A5), U31.5 (A5)
MEMADDR6: J6.5, U30.4 (A6), U31.4 (A6)
MEMADDR7: J6.6, U30.3 (A7), U31.3 (A7)
MEMADDR8: J6.3, U30.25 (A8), U31.25 (A8)
MEMADDR9: J6.4, U30.24 (A9), U31.24 (A9)
MEMADDR10: J6.1, U30.21 (A10), U31.21 (A10)
unnamed: R269.2, SW3.3, U30.2 (A12), U31.2 (A12)
unnamed: R270.2, SW3.4, U30.23 (A11), U31.23 (A11)
ROM0: J4.15, U31.11 (I/O0)
ROM1: J4.16, U31.12 (I/O1)
ROM2: J4.13, U31.13 (I/O2)
ROM3: J4.14, U31.15 (I/O3)
ROM4: J4.11, U31.16 (I/O4)
ROM5: J4.12, U31.17 (I/O5)
ROM6: J4.9, U31.18 (I/O6)
ROM7: J4.10, U31.19 (I/O7)
ROM8: J4.7, U30.11 (I/O0)
ROM9: J4.8, U30.12 (I/O1)
ROM10: J4.5, U30.13 (I/O2)
ROM11: J4.6, U30.15 (I/O3)
ROM12: J4.3, U30.16 (I/O4)
ROM13: J4.4, U30.17 (I/O5)
ROM14: J4.1, U30.18 (I/O6)
ROM15: J4.2, U30.19 (I/O7)

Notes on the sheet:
To ADDR-Bus
To DATA-Bus
